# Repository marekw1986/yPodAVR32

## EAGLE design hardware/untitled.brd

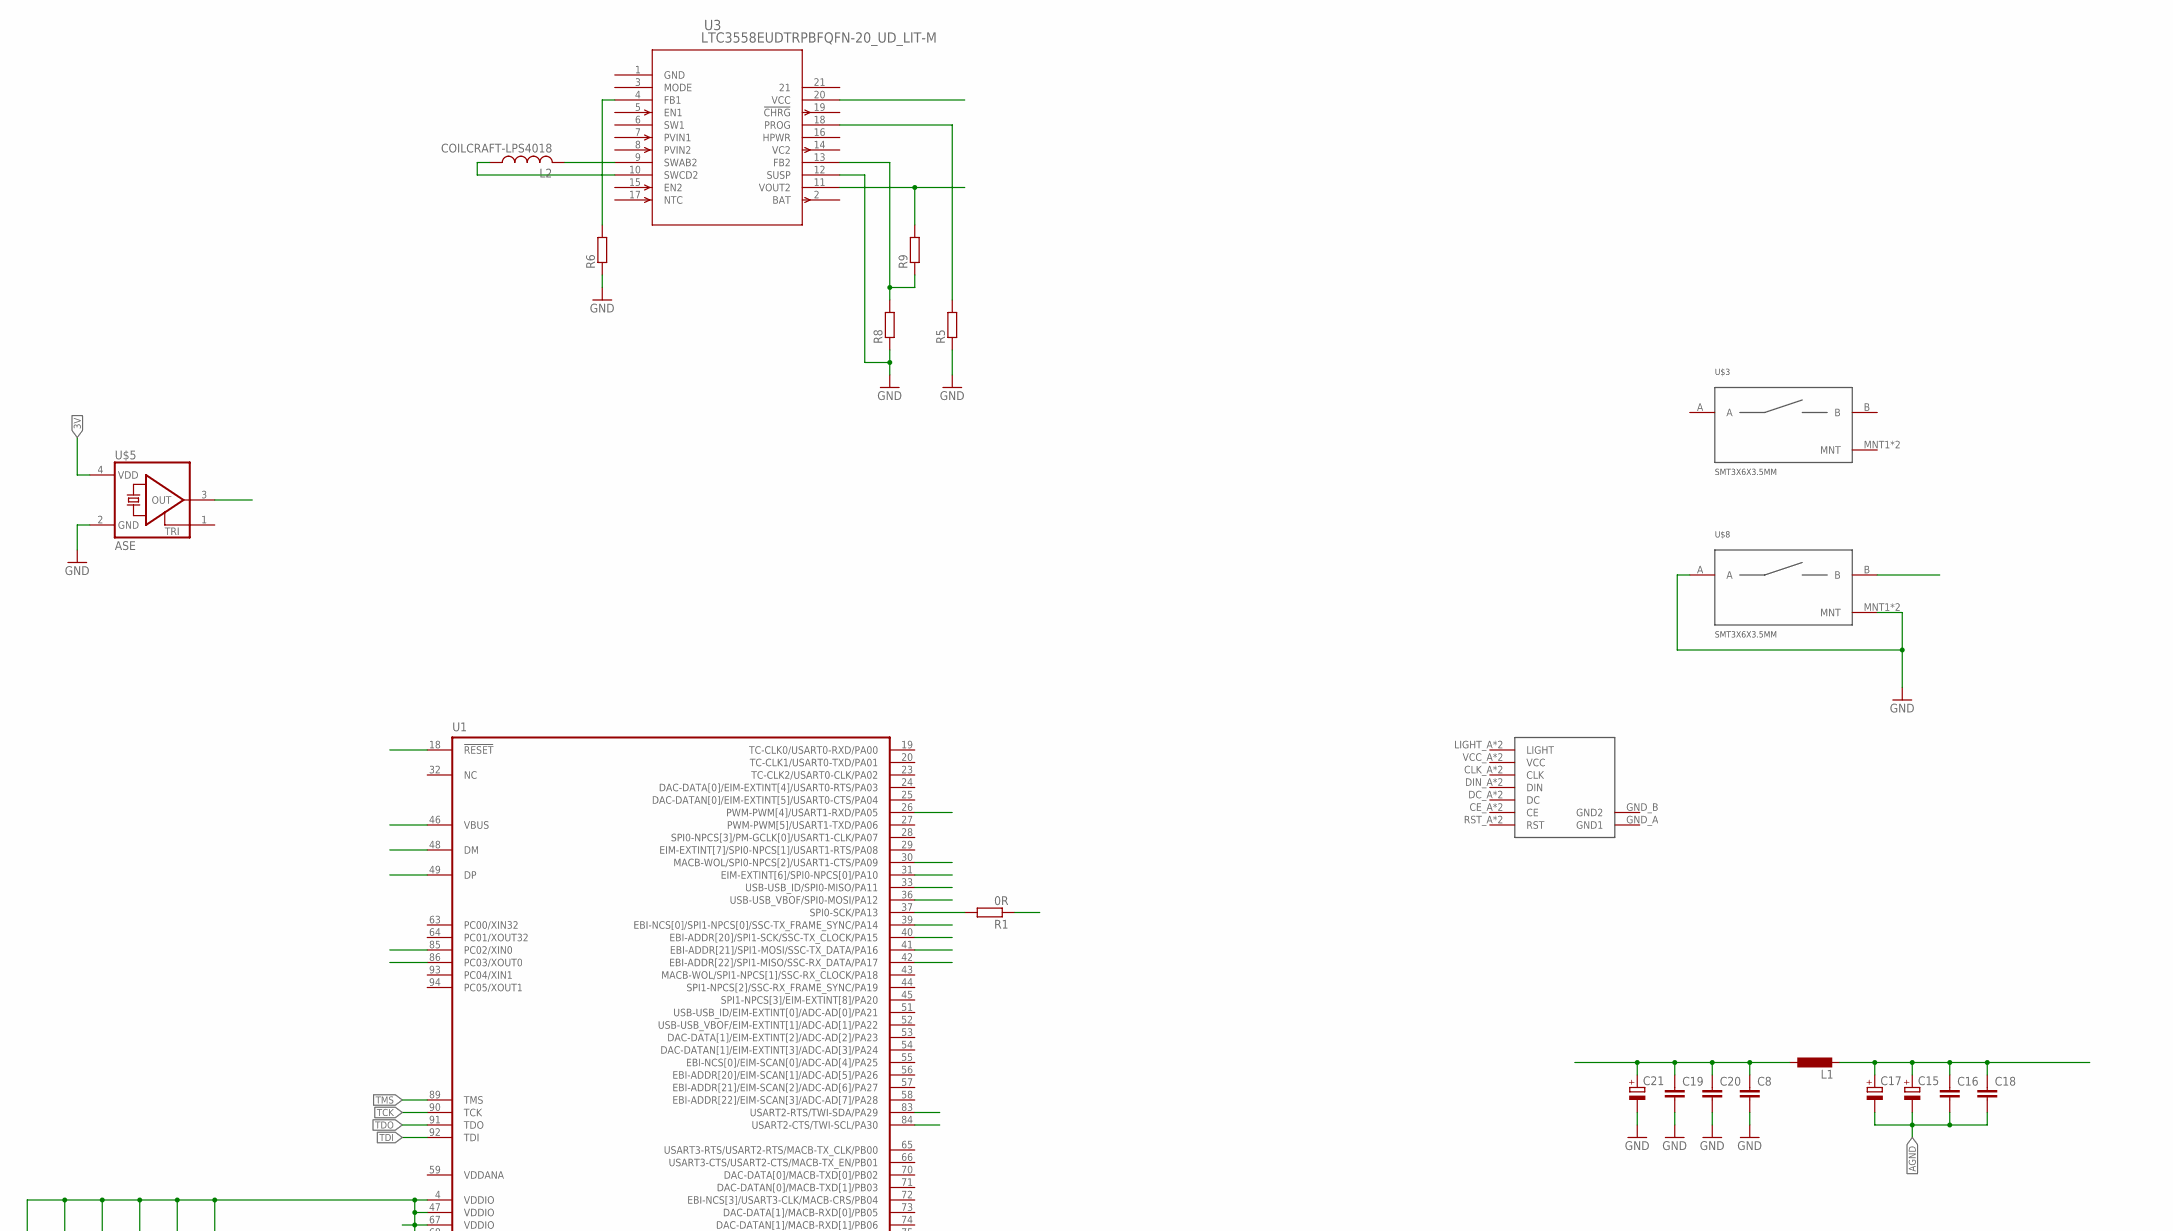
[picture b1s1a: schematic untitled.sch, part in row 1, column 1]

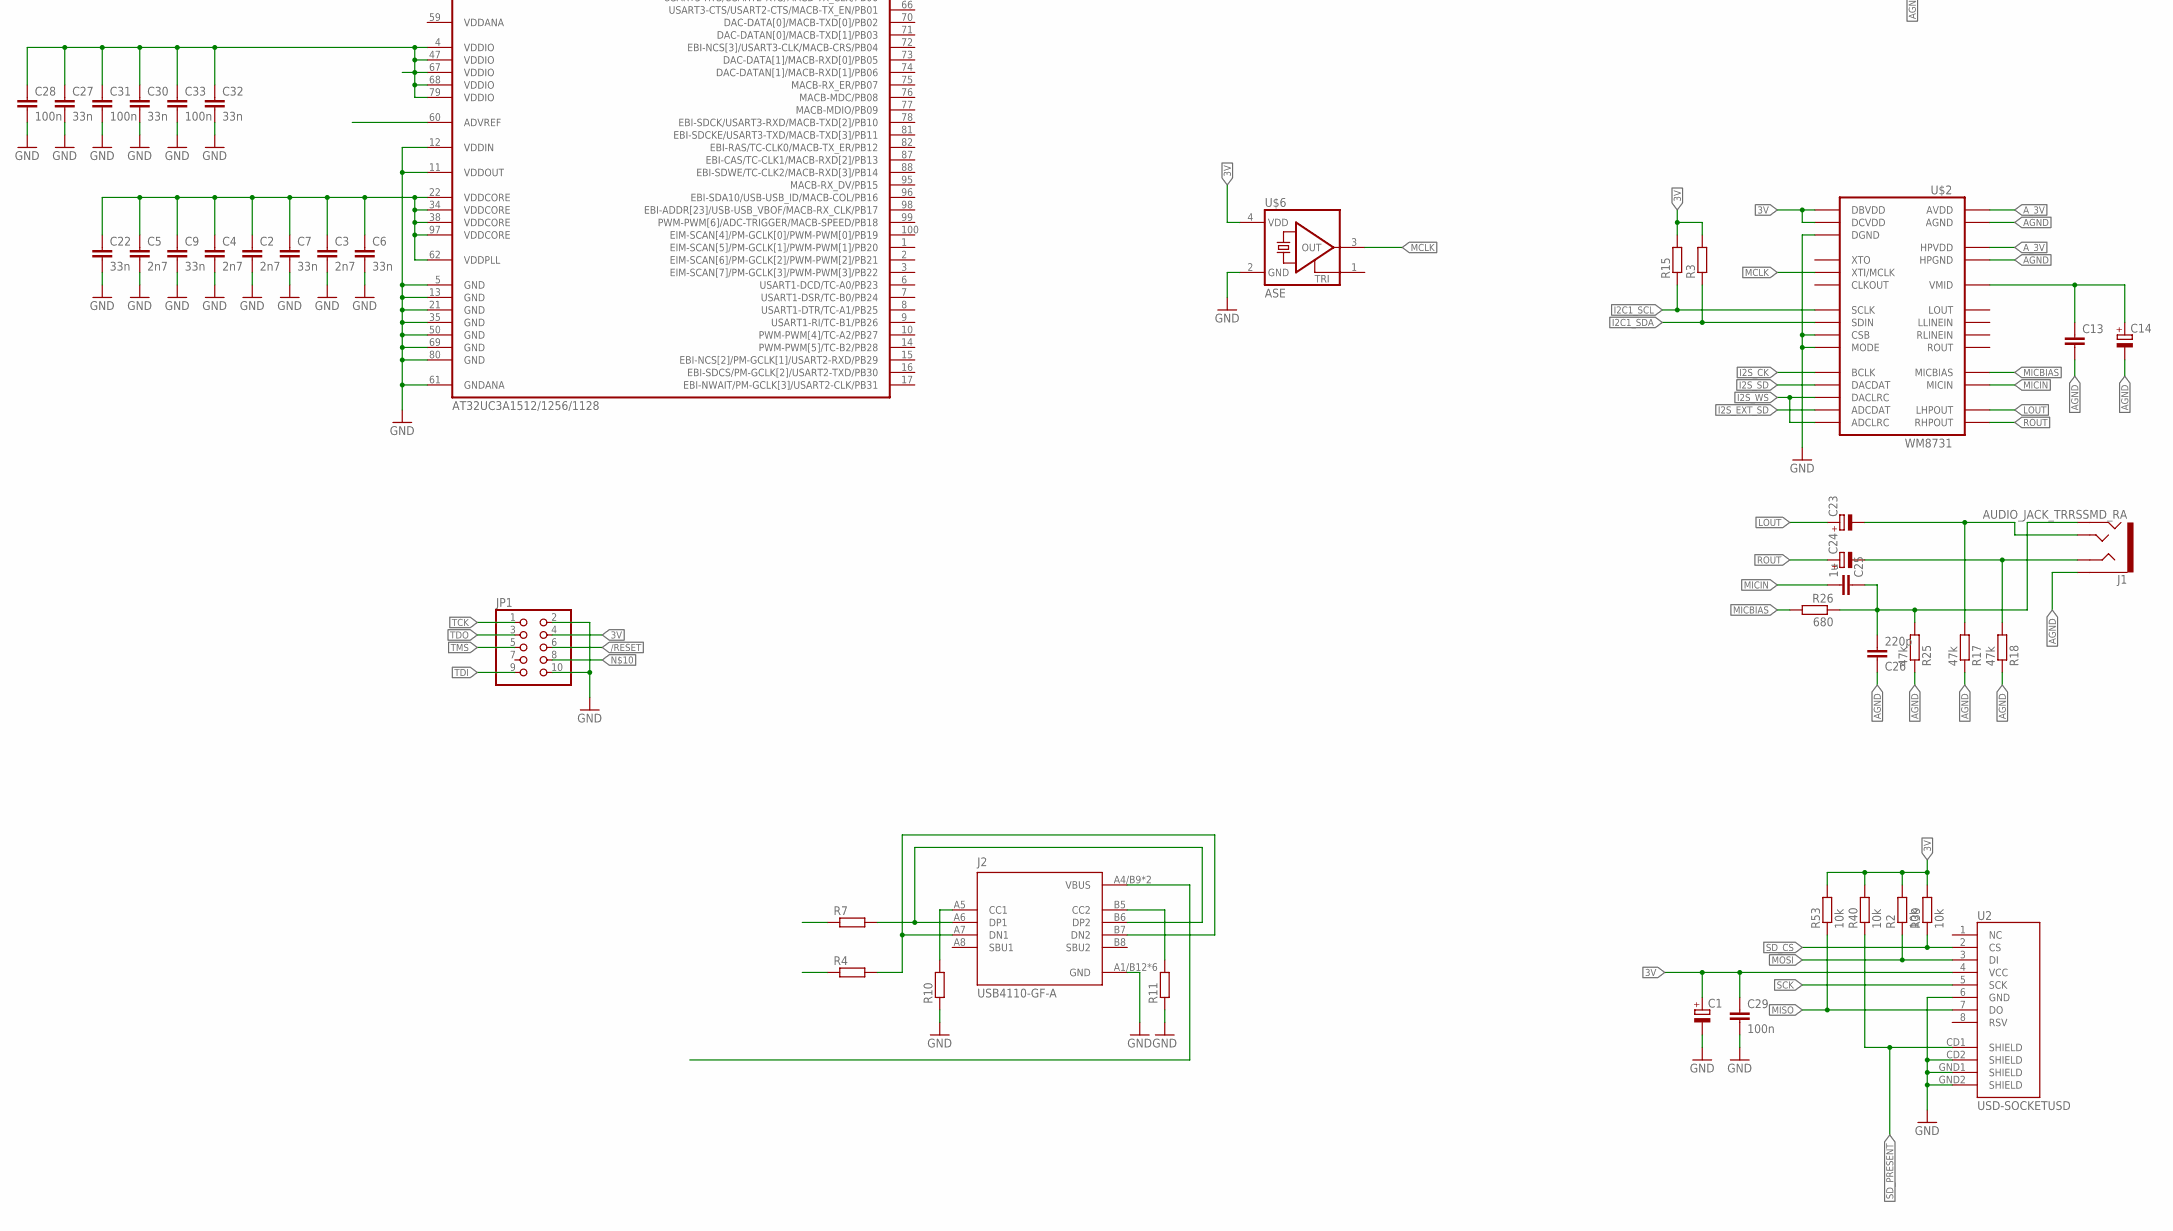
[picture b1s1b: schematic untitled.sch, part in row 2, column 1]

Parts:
C1, C14, C15, C17, C21: CPOL-EUSMCA; SMC_A
C2, C3, C4, C5: 2n7; C0402
C6, C7, C9, C22, C27, C30, C32: 33n; C0402
C8, C20: C-EUC0402; C0402
C13, C16, C18, C19: C-EUC0603; C0603
C23, C24: CPOL-EUSMCE; SMC_E
C25: 1u; C0603
C26: 220p; C0603
C28, C31, C33: 100n; C0402
C29: 100n; C0603
J1: AUDIO_JACK_TRRSSMD_RA; AUDIO_JACK_3.5MM_TRRS_SMD_RA
J2: USB4110-GF-A; GCT_USB4110-GF-A
JP1: PINHD-2X5; 2X05
L1: L-EUL3225M; L3225M
L2: COILCRAFT-LPS4018; LPS4018
R1: 0R; R0603
R2: 10k; R0402
R3, R4, R5, R6, R7, R8, R9, R10, R11, R15: R-EU_R0402; R0402
R17, R18, R25: 47k; R0603
R26: 680; R0603
R39, R40, R53: 10k; R0603
U1: AT32UC3A1512/1256/1128; TQFP100
U2: USD-SOCKETUSD; USD-SOCKET-PP
U3: LTC3558EUDTRPBFQFN-20_UD_LIT-M; QFN-20_UD_LIT-M
U$1: NOKIA5110_LCD
U$2: WM8731; 28-SSOP
U$3, U$8: SMT3X6X3.5MM
U$5, U$6: ASE

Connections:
3V: C1.+, C8.1, C19.1, C20.1, C21.+, C27.1, C28.1, C29.1, C30.1, C31.1, C32.1, C33.1, JP1.4, L1.1, R2.2, R3.2, R9.2, R15.2, R39.2, R40.2, R53.2, U1.4 (VDDIO), U1.47 (VDDIO), U1.60 (ADVREF), U1.67 (VDDIO), U1.68 (VDDIO), U1.79 (VDDIO), U2.4 (VCC), U3.11 (VOUT2), U$2.P$1 (DBVDD), U$2.P$27 (DCVDD), U$5.4 (VDD), U$6.4 (VDD)
/RESET: JP1.6, U1.18 (!RESET)
AGND: C13.2, C14.-, C15.-, C16.2, C17.-, C18.2, C26.1, J1.EARTH, R17.1, R18.1, R25.1, U$2.P$11 (HPGND), U$2.P$15 (AGND)
A_3V: C15.+, C16.1, C17.+, C18.1, L1.2, U$2.P$8 (HPVDD), U$2.P$14 (AVDD)
D2_N: J2.A7 (DN1), J2.B7 (DN2), R4.2
D2_P: J2.A6 (DP1), J2.B6 (DP2), R7.2
D_N: R4.1, U1.48 (DM)
D_P: R7.1, U1.49 (DP)
GND: C1.-, C2.2, C3.2, C4.2, C5.2, C6.2, C7.2, C8.2, C9.2, C19.2, C20.2, C21.-, C22.2, C27.2, C28.2, C29.2, C30.2, C31.2, C32.2, C33.2, J2.A1/B12 (GND), J2.B1/A12 (GND), J2.S1 (GND), J2.S2 (GND), J2.S3 (GND), J2.S4 (GND), JP1.2, JP1.10, R5.1, R6.1, R8.1, R10.1, R11.1, U1.5 (GND), U1.11 (VDDOUT), U1.12 (VDDIN), U1.13 (GND), U1.21 (GND), U1.35 (GND), U1.50 (GND), U1.61 (GNDANA), U1.69 (GND), U1.80 (GND), U2.6 (GND), U2.CD2 (SHIELD), U2.GND1 (SHIELD), U2.GND2 (SHIELD), U3.1 (GND), U3.12 (SUSP), U$2.P$21 (MODE), U$2.P$22 (CSB), U$2.P$28 (DGND), U$5.2 (GND), U$6.2 (GND), U$8.A, U$8.MNT1 (MNT), U$8.MNT2 (MNT)
I2C1_SCL: R15.1, U1.84 (USART2-CTS/TWI-SCL/PA30), U$2.P$24 (SCLK)
I2C1_SDA: R3.1, U1.83 (USART2-RTS/TWI-SDA/PA29), U$2.P$23 (SDIN)
I2S_CK: U1.40 (EBI-ADDR[20]/SPI1-SCK/SSC-TX_CLOCK/PA15), U$2.P$3 (BCLK)
I2S_EXT_SD: U1.42 (EBI-ADDR[22]/SPI1-MISO/SSC-RX_DATA/PA17), U$2.P$6 (ADCDAT)
I2S_SD: U1.41 (EBI-ADDR[21]/SPI1-MOSI/SSC-TX_DATA/PA16), U$2.P$4 (DACDAT)
I2S_WS: U1.39 (EBI-NCS[0]/SPI1-NPCS[0]/SSC-TX_FRAME_SY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), U$2.P$5 (DACLRC), U$2.P$7 (ADCLRC)
KEY_VOLUP: U1.26 (PWM-PWM[4]/USART1-RXD/PA05), U$8.B
LOUT: C23.+, U$2.P$9 (LHPOUT)
MCLK: U$2.P$25 (XTI/MCLK), U$6.3 (OUT)
MICBIAS: R26.2, U$2.P$17 (MICBIAS)
MICIN: C25.2, U$2.P$18 (MICIN)
MISO: R53.1, U1.33 (USB-USB_ID/SPI0-MISO/PA11), U2.7 (DO)
MOSI: R2.1, U1.36 (USB-USB_VBOF/SPI0-MOSI/PA12), U2.3 (DI)
unnamed: R1.2, U1.37 (SPI0-SCK/PA13)
unnamed: L2.2, U3.9 (SWAB2)
unnamed: L2.1, U3.10 (SWCD2)
unnamed: R5.2, U3.18 (PROG)
unnamed: R6.2, U3.4 (FB1)
unnamed: R8.2, R9.1, U3.13 (FB2)
unnamed: J2.B5 (CC2), R11.2
unnamed: J2.A5 (CC1), R10.2
unnamed: C13.1, C14.+, U$2.P$16 (VMID)
unnamed: C23.-, J1.TIP, R17.2
unnamed: C24.-, J1.RING1, R18.2
unnamed: C25.1, C26.2, J1.RING2, R25.2, R26.1
OSC_IN: U1.85 (PC02/XIN0), U$5.3 (OUT)
OSC_OUT: U1.86 (PC03/XOUT0)
ROUT: C24.+, U$2.P$10 (RHPOUT)
SCK: R1.1, U2.5 (SCK)
SD_CS: R39.1, U1.31 (EIM-EXTINT[6]/SPI0-NPCS[0]/PA10), U2.2 (CS)
SD_PRESENT: R40.1, U1.30 (MACB-WOL/SPI0-NPCS[2]/USART1-CTS/PA09), U2.CD1 (SHIELD)
TCK: JP1.1, U1.90 (TCK)
TDI: JP1.9, U1.92 (TDI)
TDO: JP1.3, U1.91 (TDO)
TMS: JP1.5, U1.89 (TMS)
VBUS: J2.A4/B9 (VBUS), J2.B4/A9 (VBUS), U1.46 (VBUS), U3.20 (VCC)
VDDANA: U1.59 (VDDANA)
VDDCORE: C2.1, C3.1, C4.1, C5.1, C6.1, C7.1, C9.1, C22.1, U1.22 (VDDCORE), U1.34 (VDDCORE), U1.38 (VDDCORE), U1.62 (VDDPLL), U1.97 (VDDCORE)

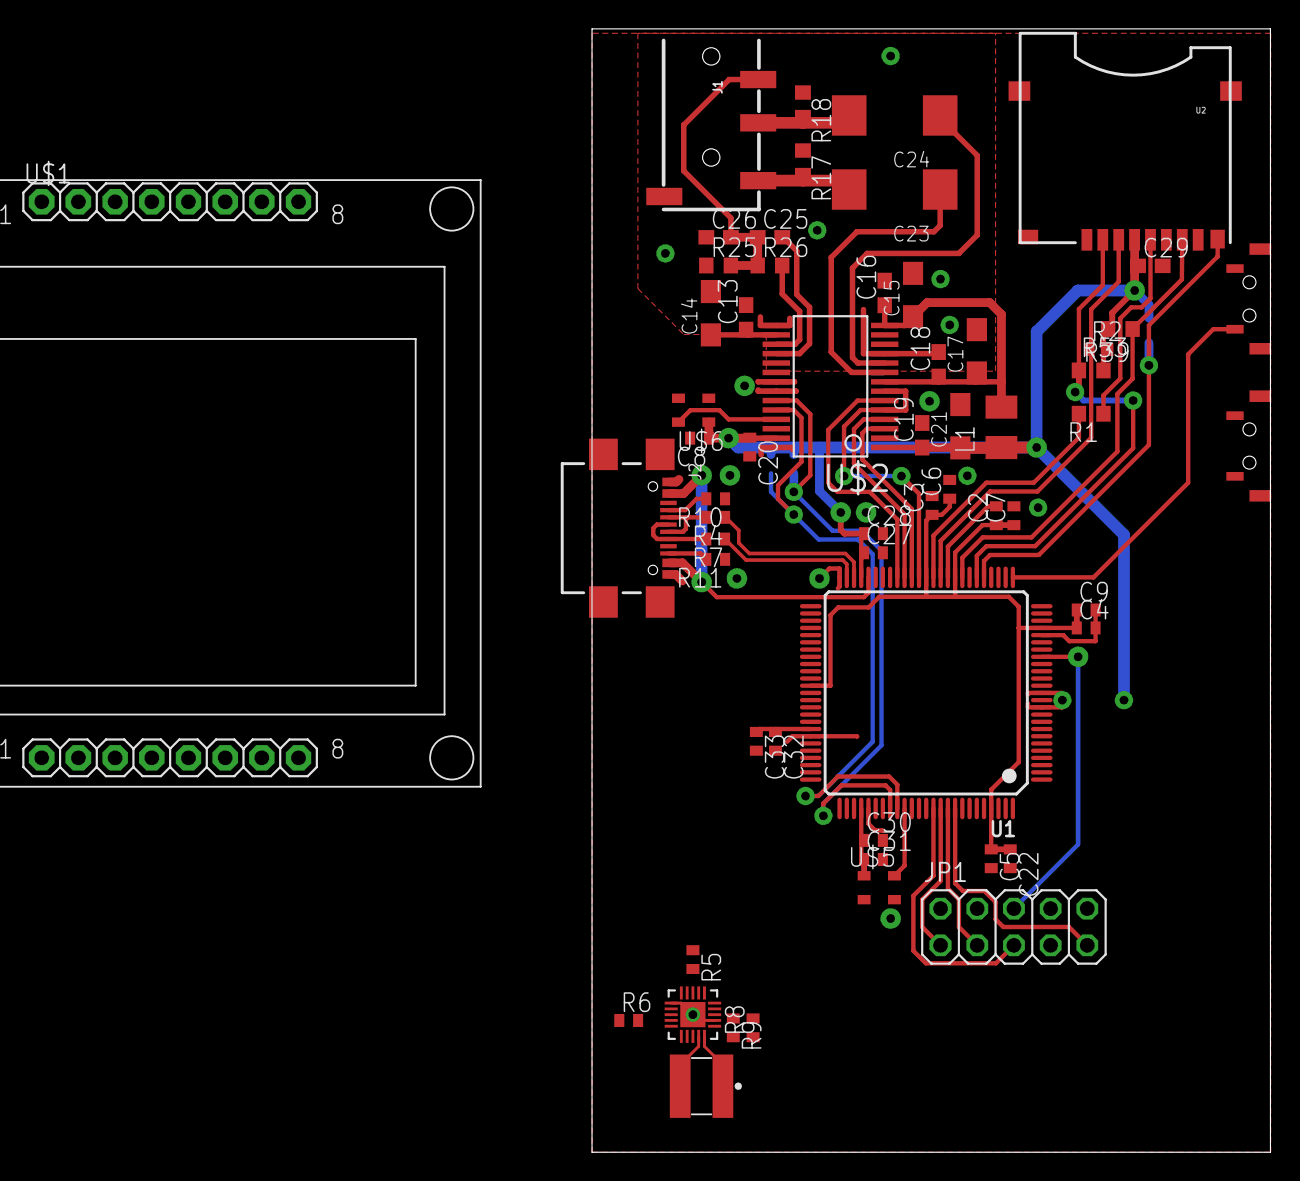
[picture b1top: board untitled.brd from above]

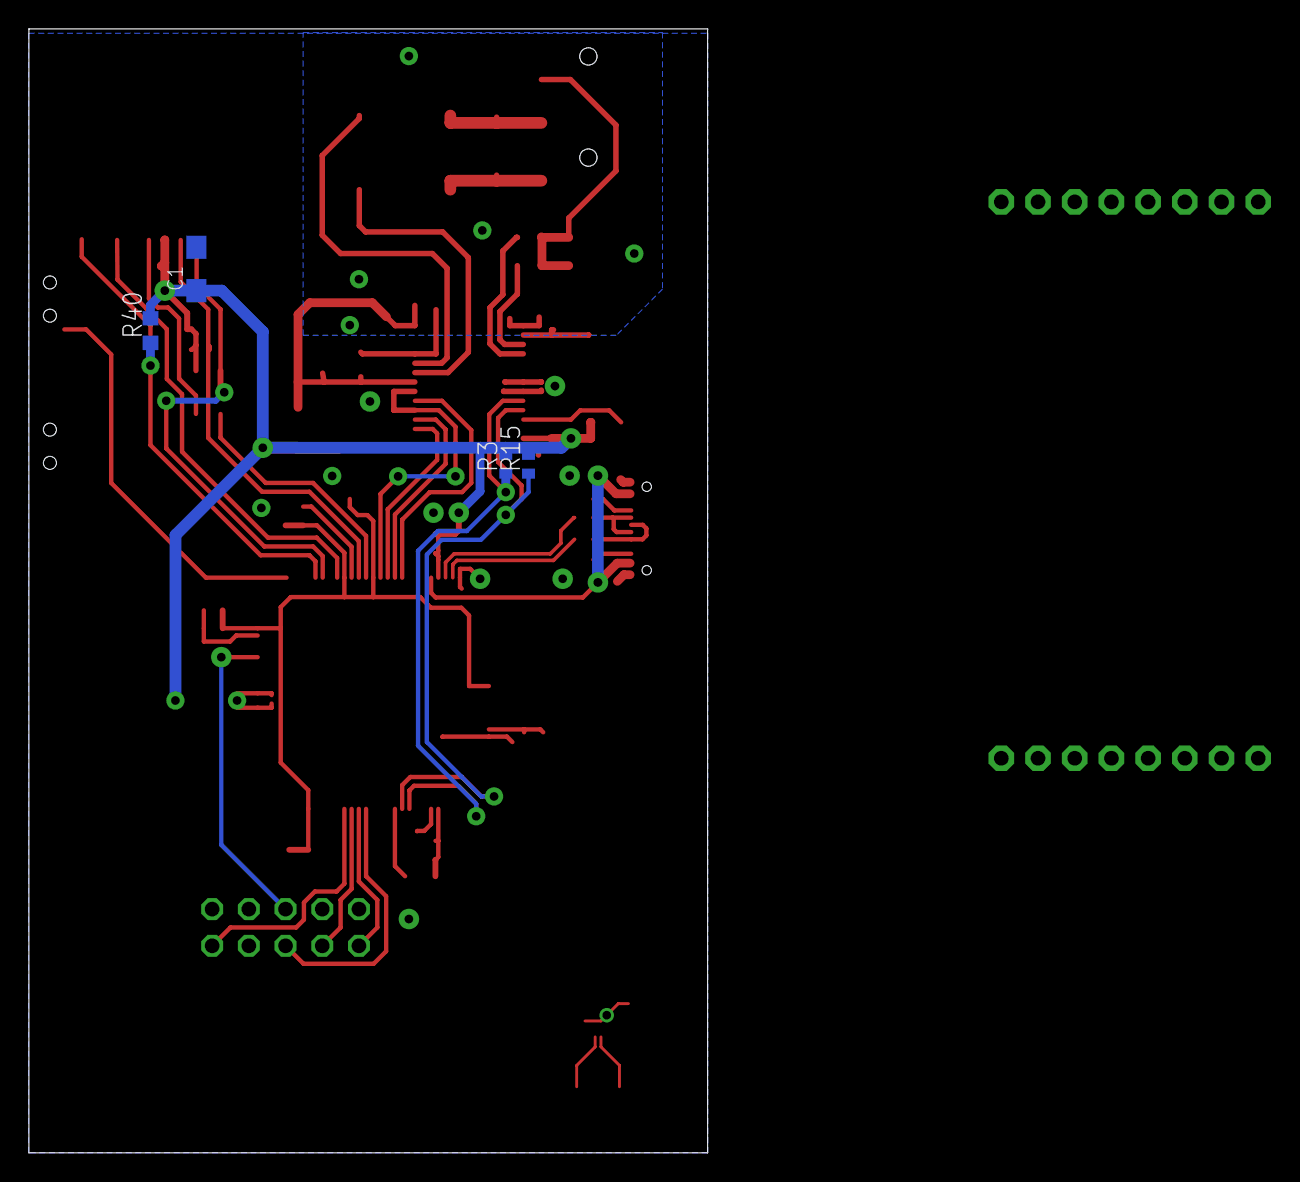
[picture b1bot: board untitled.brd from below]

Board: 2 copper layers, 47.0 x 77.8 mm, 63 parts (4 on the bottom side), 45 nets.

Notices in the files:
parts and their libraries:
atmel-avr32: Copyright (C) 2008, Bob Starr
SparkFun-Connectors: Licensing: Creative Commons ShareAlike 4.0 International - https://creativecommons.org/licenses/by-sa/4.0
COPYRIGHT: Copyright (C) 2026 Ultra Librarian. All rights reserved.
